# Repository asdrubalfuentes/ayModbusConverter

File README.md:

# ayModbusConverter

**Conversor Modbus TCP ⇄ Modbus RTU (RS-485 y RS-232)** de Aysafi, basado en la placa **WT32-ETH01** (ESP32 + Ethernet LAN8720), con pantalla OLED de 0.96" y configuración web con asistente.

La base es un **servidor Modbus TCP transparente**: cada petición que llega por la LAN se enruta por Unit ID a uno de los dos puertos serie y la respuesta del esclavo vuelve sin tocar. El mapa de memoria es el del equipo RTU conectado. Sobre esa base estándar, Aysafi agrega estados de transmisión visibles, asistente con detección automática, protección del bus (esclavos caídos, caché, solo lectura) e integración con MQTT y API REST.

```
                                                    ┌── P1 RS-485 ──► esclavos (Unit ID 1-100)
 SCADA / HMI / PLC ──LAN (Modbus TCP :502)──► ayModbusConverter
 nube Aysafi ◄── MQTT / API REST ──┘                └── P2 RS-232 ──► equipo (Unit ID 101 → ID 1)
                                        ▲
                teléfono / PC ──WiFi AP (portal cautivo, solo configuración)
```

## Características

### Base estándar

| Área | Detalle |
|---|---|
| LAN (servicio) | Ethernet 10/100. DHCP o IP fija con máscara, puerta de enlace, DNS 1 y 2. Nombre de host, mDNS (`<host>.local`) |
| WiFi | **Solo** punto de acceso con **portal cautivo** para configurar. No transporta tráfico Modbus |
| Modbus TCP | Servidor en :502, hasta 8 clientes, cierre por inactividad, TCP keep-alive, lista blanca de IP/redes. Modbus TCP (MBAP) o RTU sobre TCP |
| Puertos serie | P1 RS-485 (DE/RE por hardware) y P2 RS-232 (o RS-485 autodireccional). 1200 a 230400 bps, 7/8 bits, N/E/O, 1/2 bits de parada |
| Unit ID | Cada puerto atiende un rango de Unit ID con offset. Esclavo fijo opcional. Unit ID 0 = broadcast a todos los puertos |
| Temporización | Timeout, reintentos, fin de trama (t3.5 automático o manual), pausa entre peticiones, pausa tras broadcast, retardo inicial |
| Excepciones | 0x0B (el esclavo no responde), 0x0A (ruta no disponible), 0x01 (solo lectura); desactivables |
| Sistema | Usuario y clave (HTTP Basic), NTP/zona horaria, respaldo y restauración (JSON), valores de fábrica, OTA web y desde GitHub Releases |

### Mejoras Aysafi

| Mejora | Qué hace |
|---|---|
| **Estados de transmisión** | **OK / FALLAS / DESCONECTADO / SIN TRÁFICO** por puerto, por esclavo y global, más **LAN DESCONECTADA**. Se ven en el OLED (página de estado grande que parpadea ante fallas y se enciende sola al cambiar), en el banner del portal y por MQTT |
| **Asistente de puesta en marcha** | Se abre solo en un equipo nuevo: nombre y clave, red LAN, puerto serie con **detección automática**, búsqueda e identificación de equipos, y **ficha de instalación imprimible** |
| **Detección automática del puerto** | Encuentra baudios y paridad. *Activa:* consulta los Unit ID indicados en 24 combinaciones. *Pasiva:* solo escucha el tráfico de otro maestro, sin transmitir |
| **Exploración de equipos** | Lee fabricante, modelo y versión (FC43, si el equipo la soporta) y descubre qué rangos de registros existen, por bloques |
| **Esclavos caídos** | Tras N timeouts seguidos el esclavo queda "caído": se responde 0x0B al instante (sin frenar al resto del bus) y se lo reintenta en segundo plano |
| **Modo caché / agente** | El conversor sondea una tabla de lecturas y responde desde memoria: varios SCADA no saturan un bus lento. Las escrituras invalidan la caché y van directo al esclavo |
| **Aprendizaje del polling** | Anota qué lecturas hace el SCADA y cada cuánto, y las pasa a la tabla de sondeo con un clic |
| **Solo lectura** | Bloquea escrituras a esclavos y rangos de direcciones elegidos (excepción 0x01) |
| **MQTT** | Estado con LWT, valores de la tabla de sondeo y comandos de lectura/escritura (`<base>/cmd`). TLS, por defecto hacia `emqx.aysafi.com` |
| **API REST** | `/api/read`, `/api/write`, `/api/tags` en JSON, con clave de API (`X-API-Key`) o HTTP Basic |
| **Captura para Wireshark** | El monitor de tráfico se descarga como `.pcapng` (RTU y MBAP) |

## Parámetros estándar de la industria

La base sigue los parámetros que tienen en común los conversores comerciales más usados (Moxa MGate MB3180/MB3280, USR-TCP232-410S/USR-M100, Waveshare RS485-to-ETH, Elfin EE11/EW11), con los mismos nombres y comportamiento.

| Parámetro estándar | Moxa | USR | Waveshare/Elfin | ayModbusConverter |
|---|:-:|:-:|:-:|---|
| IP fija / DHCP, máscara, gateway, DNS | ✓ | ✓ | ✓ | Red → LAN |
| Baudios, bits de datos, paridad, bits de parada | ✓ | ✓ | ✓ | Puertos serie |
| Puerto TCP local (502) | ✓ | ✓ | ✓ | Modbus TCP → Puerto |
| Máximo de conexiones | ✓ | ✓ | ✓ | Conexiones simultáneas (1-8) |
| Modbus TCP ⇄ RTU / RTU sobre TCP | ✓ | ✓ | ✓ | Protocolo |
| Timeout de respuesta | ✓ | ✓ | ✓ | Puertos serie → Timeout |
| Timeout entre caracteres / fin de trama | ✓ | ✓ | ✓ | Fin de trama (0 = t3.5) |
| Retardo entre tramas | ✓ | – | ✓ | Pausa entre peticiones |
| Reintentos | ✓ | – | – | Reintentos |
| Retardo inicial | ✓ | – | – | Modbus TCP → Retardo inicial |
| Excepción de pasarela (0x0A/0x0B) | ✓ | ✓ | – | Responder excepciones |
| Mapeo de Unit ID por puerto (rango + offset) | ✓ | – | – | Puertos serie → Enrutamiento |
| TCP alive check | ✓ | ✓ | ✓ | TCP alive check (s) |
| Cierre por inactividad | ✓ | ✓ | ✓ | Cierre por inactividad (s) |
| Lista de IP permitidas | ✓ | – | – | Control de acceso |
| Monitor de tráfico / diagnóstico | ✓ | ✓ | – | Diagnóstico |
| Actualización de firmware web | ✓ | ✓ | ✓ | Sistema → Firmware |
| Respaldo / restauración de la configuración | ✓ | ✓ | – | Sistema → Respaldo |
| Contraseña de administrador | ✓ | ✓ | ✓ | Sistema → Acceso |

## Hardware

### Conexiones (WT32-ETH01 v1.4)

| Función | GPIO | Serigrafía | Conectar a |
|---|---|---|---|
| P1 RS-485 RX | 5 | RXD / IO5 | RO del transceptor RS-485 |
| P1 RS-485 TX | 17 | TXD / IO17 | DI del transceptor RS-485 |
| P1 RS-485 DE//RE | 33 | 485_EN | DE y /RE unidos |
| P2 RS-232 RX | 35 | IO35 | R1OUT del MAX3232 |
| P2 RS-232 TX | 4 | IO4 | T1IN del MAX3232 |
| OLED SDA | 14 | IO14 | SDA del SSD1306 (0x3C) |
| OLED SCL | 15 | IO15 | SCL del SSD1306 |
| Botón | 32 | CFG | pulsador a GND (pull-up interno) |
| LED actividad | 2 | IO2 | LED + 1 kΩ a GND (opcional) |
| Programación | 1 / 3 | TX0 / RX0 | adaptador USB-TTL 3V3 |

- P1: transceptor MAX3485 / SP3485 (3,3 V). Con un MAX485 de 5 V, pon un divisor en RO.
- P2: MAX3232 a 3,3 V. T1OUT → RX del equipo, R1IN ← TX del equipo, GND común (en un DB9 estándar: pin 2 RX, 3 TX, 5 GND; si no hay comunicación, cruza 2 y 3). También acepta un módulo RS-485 **autodireccional**: no queda ningún GPIO de salida libre para un DE.
- Termina el bus RS-485 con 120 Ω en ambos extremos. Usa par trenzado con malla y referencia GND común.
- No uses los GPIO 0, 16, 18, 19, 21, 22, 23, 25, 26 ni 27: los usa la PHY Ethernet. El GPIO 12 debe estar en bajo al arrancar.

Detalle pin a pin, variantes de módulos y banco de pruebas: [test/README.md](test/README.md).

### Botón

| Pulsación | Acción |
|---|---|
| Corta | Siguiente página del OLED / despierta la pantalla |
| 3 s | Activa el punto de acceso de configuración |
| 10 s | Restaura los valores de fábrica y reinicia |

### Páginas del OLED

| # | Página | Contenido |
|---|---|---|
| 0 | Estado | OK / FALLAS / DESCONECTADO / SIN LAN en grande (parpadea ante fallas) y estado de cada puerto |
| 1 | Red | IP de la LAN, velocidad, AP y portal |
| 2 | Puertos | formato serie, rango de Unit ID y caché de cada puerto; clientes TCP |
| 3 | Esclavos | estado de cada esclavo visto |
| 4 | Tráfico | peticiones, OK, timeouts, CRC, excepciones, caché, latencia |
| 5 | Sistema | versión, tiempo encendido, memoria, MAC |

Un cambio de estado (cable de red, puerto que empieza a fallar o se recupera) enciende la pantalla y salta a la página de estado.

## Primer arranque

1. Conecta la LAN (DHCP por defecto) o el WiFi **`ayModbus-XXXXXX`** (clave `aysafi1234`; el portal se abre solo).
2. Entra a la IP que muestra el OLED o a `http://aymc-xxxxxx.local`. Usuario **admin**, clave **admin**.
3. El **asistente** se abre solo: nombre y clave, red, puerto serie (con *Detectar automáticamente*), búsqueda de equipos y resumen para imprimir. Al finalizar, el equipo se reinicia.

Desde el portal WiFi (red WPA2) no se pide usuario ni clave, porque los navegadores de portal cautivo de los teléfonos no manejan bien HTTP Basic. Si la clave del AP está vacía, se pide igual.

## Valores de fábrica

| Parámetro | Valor |
|---|---|
| LAN | DHCP, host `aymc-<id>` |
| AP | siempre activo, `ayModbus-<ID>` / `aysafi1234`, canal 6 |
| P1 RS-485 | habilitado, 9600 8N1, timeout 1000 ms, Unit ID 1-247, caído tras 3 timeouts (reintento 10 s) |
| P2 RS-232 | deshabilitado, 9600 8N1, Unit ID 101-147 con offset -100. Al habilitarlo, la web ajusta P1 a 1-100 |
| Modbus TCP | :502, MBAP, 4 clientes, inactividad 300 s, keep-alive 60 s, excepciones sí |
| Caché, MQTT, API key | desactivados |
| Acceso web | admin / admin |

## Compilar y programar

```bash
pio run
```

La WT32-ETH01 no tiene USB. Para la primera carga, conecta un adaptador USB-TTL de 3,3 V a TX0/RX0/GND, pon **IO0 a GND**, reinicia (EN) y ejecuta:

```bash
pio run -t upload
```

Las cargas siguientes se hacen por OTA desde **Sistema → Firmware** (`.pio/build/wt32-eth01/firmware.bin`).

Para probar la interfaz web sin la placa (usa la UI embebida y simula la API, herramientas incluidas):

```bash
python test/webmock/mock.py --wizard
```

## Publicar una versión (OTA GitHub)

1. Anota el cambio en `CHANGELOG.md` y sube `FW_SEMVER` en `src/fw_version.h`.
2. Etiqueta sobre `main`: `git tag v1.1.0 && git push origin v1.1.0`.
3. El workflow `.github/workflows/release.yml` compila y publica `firmware.bin`, `version.txt` y `firmware.sha256` como Release *latest*.
4. Los equipos con salida a internet lo instalan con **Sistema → Instalar desde GitHub**, o solos al arrancar si está activado.

El repositorio debe ser **público** para que los equipos descarguen los Releases sin token.

## MQTT

Raíz de tópicos por defecto: `aysafi/<host>`.

| Tópico | Dirección | Contenido |
|---|---|---|
| `<base>/status` | publica (retenido) | `{online, name, fw, ip, lan, state, ports[], slaves[], stats}`; cada N s y al cambiar un estado. LWT `{"online":false}` |
| `<base>/data/<nombre>` | publica | valores de cada lectura de la tabla de sondeo marcada *MQTT*: `{v:[...], q, age, uid, fc, addr, ts}` |
| `<base>/cmd` | suscribe (opcional) | `{"id":7,"uid":1,"fc":3,"addr":0,"qty":10}` o escritura `{"uid":1,"fc":6,"addr":10,"value":123}` (`port` opcional) |
| `<base>/cmd/resp` | publica | `{id, ok, result, values / exception, lat}` |

## API REST

Todas las rutas usan HTTP Basic, salvo que la petición llegue desde el AP. Las marcadas con * aceptan también la cabecera `X-API-Key` (o `?key=`).

| Método | Ruta | Uso |
|---|---|---|
| GET | `/api/status` | Estado global y por puerto/esclavo, red, contadores, clientes, MQTT |
| GET | `/api/read`* | `?uid=1&fc=3&addr=0&qty=10[&port=1][&cache=0]` lectura (enruta por Unit ID si no hay `port`) |
| POST | `/api/write`* | `{uid, fc(5/6/15/16), addr, value / values[, port]}` |
| GET | `/api/tags`* | Tabla de sondeo con sus últimos valores |
| GET / POST | `/api/config` | Leer / guardar la configuración (JSON parcial; reinicia) |
| POST | `/api/port/apply` | `{port, cfg:{...}}` aplica un puerto sin reiniciar |
| GET / POST | `/api/tool` | Herramientas: `{kind:"scan"|"detect"|"discover"|"apply"|"stop", port, ...}` y su progreso |
| GET / POST | `/api/learn` | Aprendizaje del polling: resultados / `{en, clear}` |
| GET / POST | `/api/monitor` | Tramas desde `?since=N` / `{en, clear}` |
| GET | `/api/pcap` | Monitor como captura `.pcapng` |
| POST | `/api/test` | `{port, uid, fc, addr, qty, value, values}` lectura/escritura directa |
| GET | `/api/backup` · POST `/api/restore` | Respaldo / restauración (reinicia) |
| POST | `/api/stats/reset`, `/api/reboot`, `/api/factory`, `/api/wizard/done` | Mantenimiento |
| POST | `/api/fw` · `/api/ota` | Firmware por archivo / desde GitHub |

## Estructura

```
src/
  main.cpp          arranque, botón, OTA GitHub
  config.*          configuración en NVS como JSON (sobrevive a cambios de versión)
  net.*             LAN (LAN8720) + AP con portal cautivo, mDNS, NTP
  modbus_rtu.*      puerto RTU (clase por puerto): CRC, fin de trama, reintentos, escucha pasiva
  gateway.*         tareas TCP y por puerto, colas, enrutamiento, salud/estados, caché,
                    aprendizaje, solo lectura, escaneo/autodetección/exploración, monitor y pcap
  mb_util.*         armado de peticiones y respuestas JSON (web, REST, MQTT)
  mqtt_bridge.*     puente MQTT
  web.*, web_ui.h   API REST + interfaz web embebida (con asistente)
  display.*         OLED SSD1306 (páginas de estado)
  ota_update.*      OTA desde GitHub Releases
test/webmock/       servidor para probar la UI sin la placa
test/tools/         simulador de esclavos RTU + batería de pruebas automática
```

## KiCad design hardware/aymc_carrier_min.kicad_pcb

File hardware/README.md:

# PCB base — ayModbusConverter MINI

Rev E · KiCad 8 · **70 × 58 mm**, dos capas

Placa reducida al mínimo práctico, atornillada al chasis, que a su vez va al riel DIN por los anclajes. La
WT32-ETH01 se enchufa en dos zócalos de 13 pines con el **eje largo vertical**: el RJ45
sale por la pared superior del chasis y la bornera por la inferior. La tapa solo lleva el
agujero del LED de enlace.

---

## 1. Qué lleva

| Ref | Valor | Función |
|---|---|---|
| J1 | Bornera 4 vías, paso 5,08 | A, B, +V (9–24 VDC), GND |
| J2, J3 | Zócalo hembra 1×13, paso 2,54 | WT32-ETH01, filas a **22,86 mm** |
| U1 | 7805 TO-220 | +V → 5 V |
| U2 | MAX485 DIP-8 | Transceptor RS-485 half duplex |
| C1 | 100 µF / 25 V | Salida del regulador |
| C2 | 0,33 µF | Entrada del regulador |
| C3 | 100 nF | Desacoplo del MAX485 |
| R1 | 120 Ω | Terminación entre A y B |
| R2, R3 | 1 k / 2 k | Divisor de RO, 5 V → 3,3 V |
| R4 | 1 k | Limitador del LED |
| D1 | LED 3 mm | Enlace Modbus |

La bornera admite AWG18 sin problema: taladro de 1,3 mm y pad de 2,8 mm.

---

## 2. Tres cosas que cambié respecto a lo pedido

### 2.1 Separación de los zócalos: 22,86 mm, no 24

La cota real del módulo son **22,86 mm** (0,9 pulgadas), verificada contra la huella del
datasheet V1.4. Con 24 mm el módulo sencillamente no entra: son 1,14 mm de desalineación
repartidos en 13 pines. Además 24 / 2,54 = 9,45, o sea que 24 mm ni siquiera cae en la
rejilla de 2,54 en la que están los pines.

Es el único punto donde no seguí la indicación al pie de la letra, y lo hice porque la
alternativa era una placa inservible.

### 2.2 Divisor R2 / R3 en RO

No estaba en tu lista, pero es obligatorio. El MAX485 alimentado a 5 V saca **RO a 5 V**,
y esa señal entra en IO5 del ESP32, que es de 3,3 V. Sin divisor se destruye la entrada.
R2 de 1 k y R3 de 2 k la dejan en 3,33 V.

Si prefieres quitar los dos resistores, cambia el MAX485 por un **MAX3485 o SP3485**
(mismo pinout DIP-8) alimentado a 3,3 V desde el propio módulo. Son dos componentes menos
y una fuente de error menos.

### 2.3 Condensador de salida: 25 V, no 6 V

Pediste 100 µF / 6 V sobre un bus de 5 V. Eso es 1,2× de margen, cuando lo habitual es
1,5× a 2×. Los electrolíticos pierden capacidad con la temperatura y la edad, y dentro de
un tablero cerrado envejecen rápido. Puse 25 V, que no cuesta más ni ocupa mucho más.

---

## 3. El 7805 es el punto débil de esta placa

Lo monté como pediste, pero conviene saber lo que implica:

| Entrada | 150 mA | 250 mA | 350 mA |
|---|---|---|---|
| 9 V | 0,60 W | 1,00 W | 1,40 W |
| 12 V | 1,05 W | 1,75 W | 2,45 W |
| 24 V | 2,85 W | **4,75 W** | **6,65 W** |

El consumo del WT32-ETH01 con Ethernet activo y picos de WiFi está entre 150 y 350 mA.

A 24 V de entrada el regulador tiene que disipar entre 3 y 7 W. Un TO-220 sin disipador
aguanta algo más de 1 W antes de superar los 100 °C de encapsulado. Con 7 W dentro de una
caja de inoxidable cerrada, el 7805 entra en protección térmica y el equipo se reinicia en
bucle.

Tres salidas, de menos a más trabajo:

1. **Alimentar a 9 V.** Dentro del rango que pediste y la disipación baja a 1 W. Con un
   disipador pequeño funciona.
2. **Sustituir por un K7805-2000R3.** Es un convertidor conmutado con el **mismo pinout
   SIP-3** que el 7805, así que entra en la misma huella sin tocar la placa. Rendimiento
   del 90 %, disipa menos de 0,2 W a 24 V. Cuesta unas pocas veces más que un 7805 y
   resuelve el problema entero.
3. **Dejar el 7805 con disipador** y limitar la entrada a 12 V.

La huella que puse admite las tres: los tres pines son IN, GND, OUT a paso 2,54.

---

## 4. El LED de enlace

D1 está en la posición (66, 52) de la placa, que en la caja queda a **Y = −17,3 mm,
Z = +18,5 mm** respecto al centro de la tapa.

Lo mueve IO2, que en el firmware es `PIN_LED_ACT`: parpadea con cada trama Modbus válida.
Entre paquetes queda apagado, así que un parpadeo continuo significa que hay polling en
ambos extremos, que es justo lo que querías ver.

**Necesita guía de luz.** Desde la cara superior del PCB hasta la cara interior de la tapa
hay 32,4 mm. Un LED de 3 mm soldado a ras no llega ni de lejos. Dos opciones: una guía de
luz de 3 mm de ese largo, o montar el LED sobre patillas largas de modo que la cápsula
quede a ras de la tapa. La segunda es más frágil pero no cuesta nada.

---

## 5. Ruteado

Dos capas, con plano de masa en ambas. No hay vías de señal: todos los componentes son de
agujero pasante, así que cada pad une las dos capas por sí mismo.

| Capa | Nets |
|---|---|
| F.Cu | +5V, RS485_B, P1_RO, P1_DI, RO_RAW, LED_D, LED_A |
| B.Cu | +VIN, RS485_A, P1_DE |

Tres nets van por la cara inferior porque sus cruces son topológicamente inevitables: A y B
se cruzan entre el MAX485 y la bornera, y DE cruza a RO y DI porque el orden de los pines
del MAX485 es el inverso del orden de los pines del módulo.

Anchos: 1,0 mm en alimentación, 0,5 mm en señal.

### Verificación automática

El generador comprueba, antes de escribir el archivo:

- pads que se solapan
- pistas que pasan sobre pads de otra red
- cruces entre pistas de distinta red en la misma capa
- pads con red pero sin pista que los toque
- componentes fuera del contorno

Las cinco pasan. Cuatro de ellas fallaron en la primera pasada y señalaron errores reales:
la pista de +5 V pasaba por encima del pad de masa del propio C1, y la del LED bajaba justo
por la columna de pads de la fila B y pisaba el pin 14.

---

## 6. Conexiones al módulo

| Pin del módulo | Señal | Va a |
|---|---|---|
| 7 (IO5) | RO | Divisor R2/R3 |
| 8 (IO17) | DI | U2 pin 4 |
| 6 (IO33) | DE + RE̅ | U2 pines 2 y 3 |
| 12 | 5 V | Salida del 7805 |
| 15 (IO2) | LED | R4 → D1 |
| 2, 9, 11, 14, 23 | GND | Plano |

Coinciden con `src/board.h` del firmware. Los demás pines quedan sin conectar.

---

## 7. Lo que esta placa no lleva

Por simplificar quedaron fuera tres cosas que conviene tener presentes:

- **Sin cabecera de programación.** La primera grabación hay que hacerla con el módulo
  fuera de la placa, con un adaptador USB-TTL. Después todo va por OTA.
- **Sin botón CFG.** El firmware usa IO32 para levantar el AP de WiFi y para los valores de
  fábrica. Sin botón, la configuración es solo por Ethernet o por la consola serie del
  módulo desenchufado.
- **Sin protección de entrada.** No hay fusible, ni diodo antiinversión, ni TVS en el bus.
  Si el equipo va a un tablero industrial con maniobra inductiva cerca, merece la pena
  añadir al menos una SM712 entre A, B y GND.

Ninguna impide que funcione; las tres son decisiones conscientes.

---

## 8. Archivos

| Archivo | Contenido |
|---|---|
| `aymc_carrier_min.kicad_pcb` | Placa ruteada |
| `aymc_carrier_min.kicad_sch` | Esquema |
| `aymc.kicad_sym` | Símbolos |
| `pcb_preview.png` | Vista del trazado |
| `netlist.csv` | 11 redes |
| `bom.csv` | Lista de materiales |
| `tools/gen_pcb.py` | Genera placa, netlist y BOM, y verifica el ruteado |
| `tools/gen_sch.py` | Genera el esquema desde la misma tabla |

Esquema y placa salen de **una sola tabla de componentes y redes**, así que no pueden
desincronizarse. Si cambias algo, cámbialo en `gen_pcb.py` y vuelve a ejecutar los dos.

---

## 9. Reducción respecto a la Rev D

| Concepto | Rev D | Rev E | Reducción |
|---|---|---|---|
| Placa | 95 × 72 mm | **70 × 58 mm** | 41 % de área |
| Interior de la caja | 104 × 82 × 40 | **78 × 68 × 36** | 44 % de volumen |
| Chapa bruta | 366 cm² | **249 cm²** | 32 % |
| Masa de inoxidable | 289 g | **197 g** | 32 % |

Qué permitió apretarla:

- El MAX485, el divisor y la terminación se agruparon en la columna derecha junto a la
  bornera, en vez de repartirse por la placa.
- Los taladros de fijación pasaron a 5 mm del borde y la alimentación cruza por el borde
  superior, a 2,5 mm, que es donde no estorba a nada.
- El ancho de pista en señal bajó a 0,25 mm, lo justo para pasar entre pads a paso 2,54
  con 0,2 mm de holgura. La alimentación se mantiene en 0,8 mm.

El límite ahora lo pone el propio módulo: 60 mm de largo con el RJ45 asomando, más la
bornera debajo sin solaparse con él. Para bajar de 58 mm de alto habría que mover la
bornera a un costado, y entonces saldría por la tapa en vez de por el chasis.

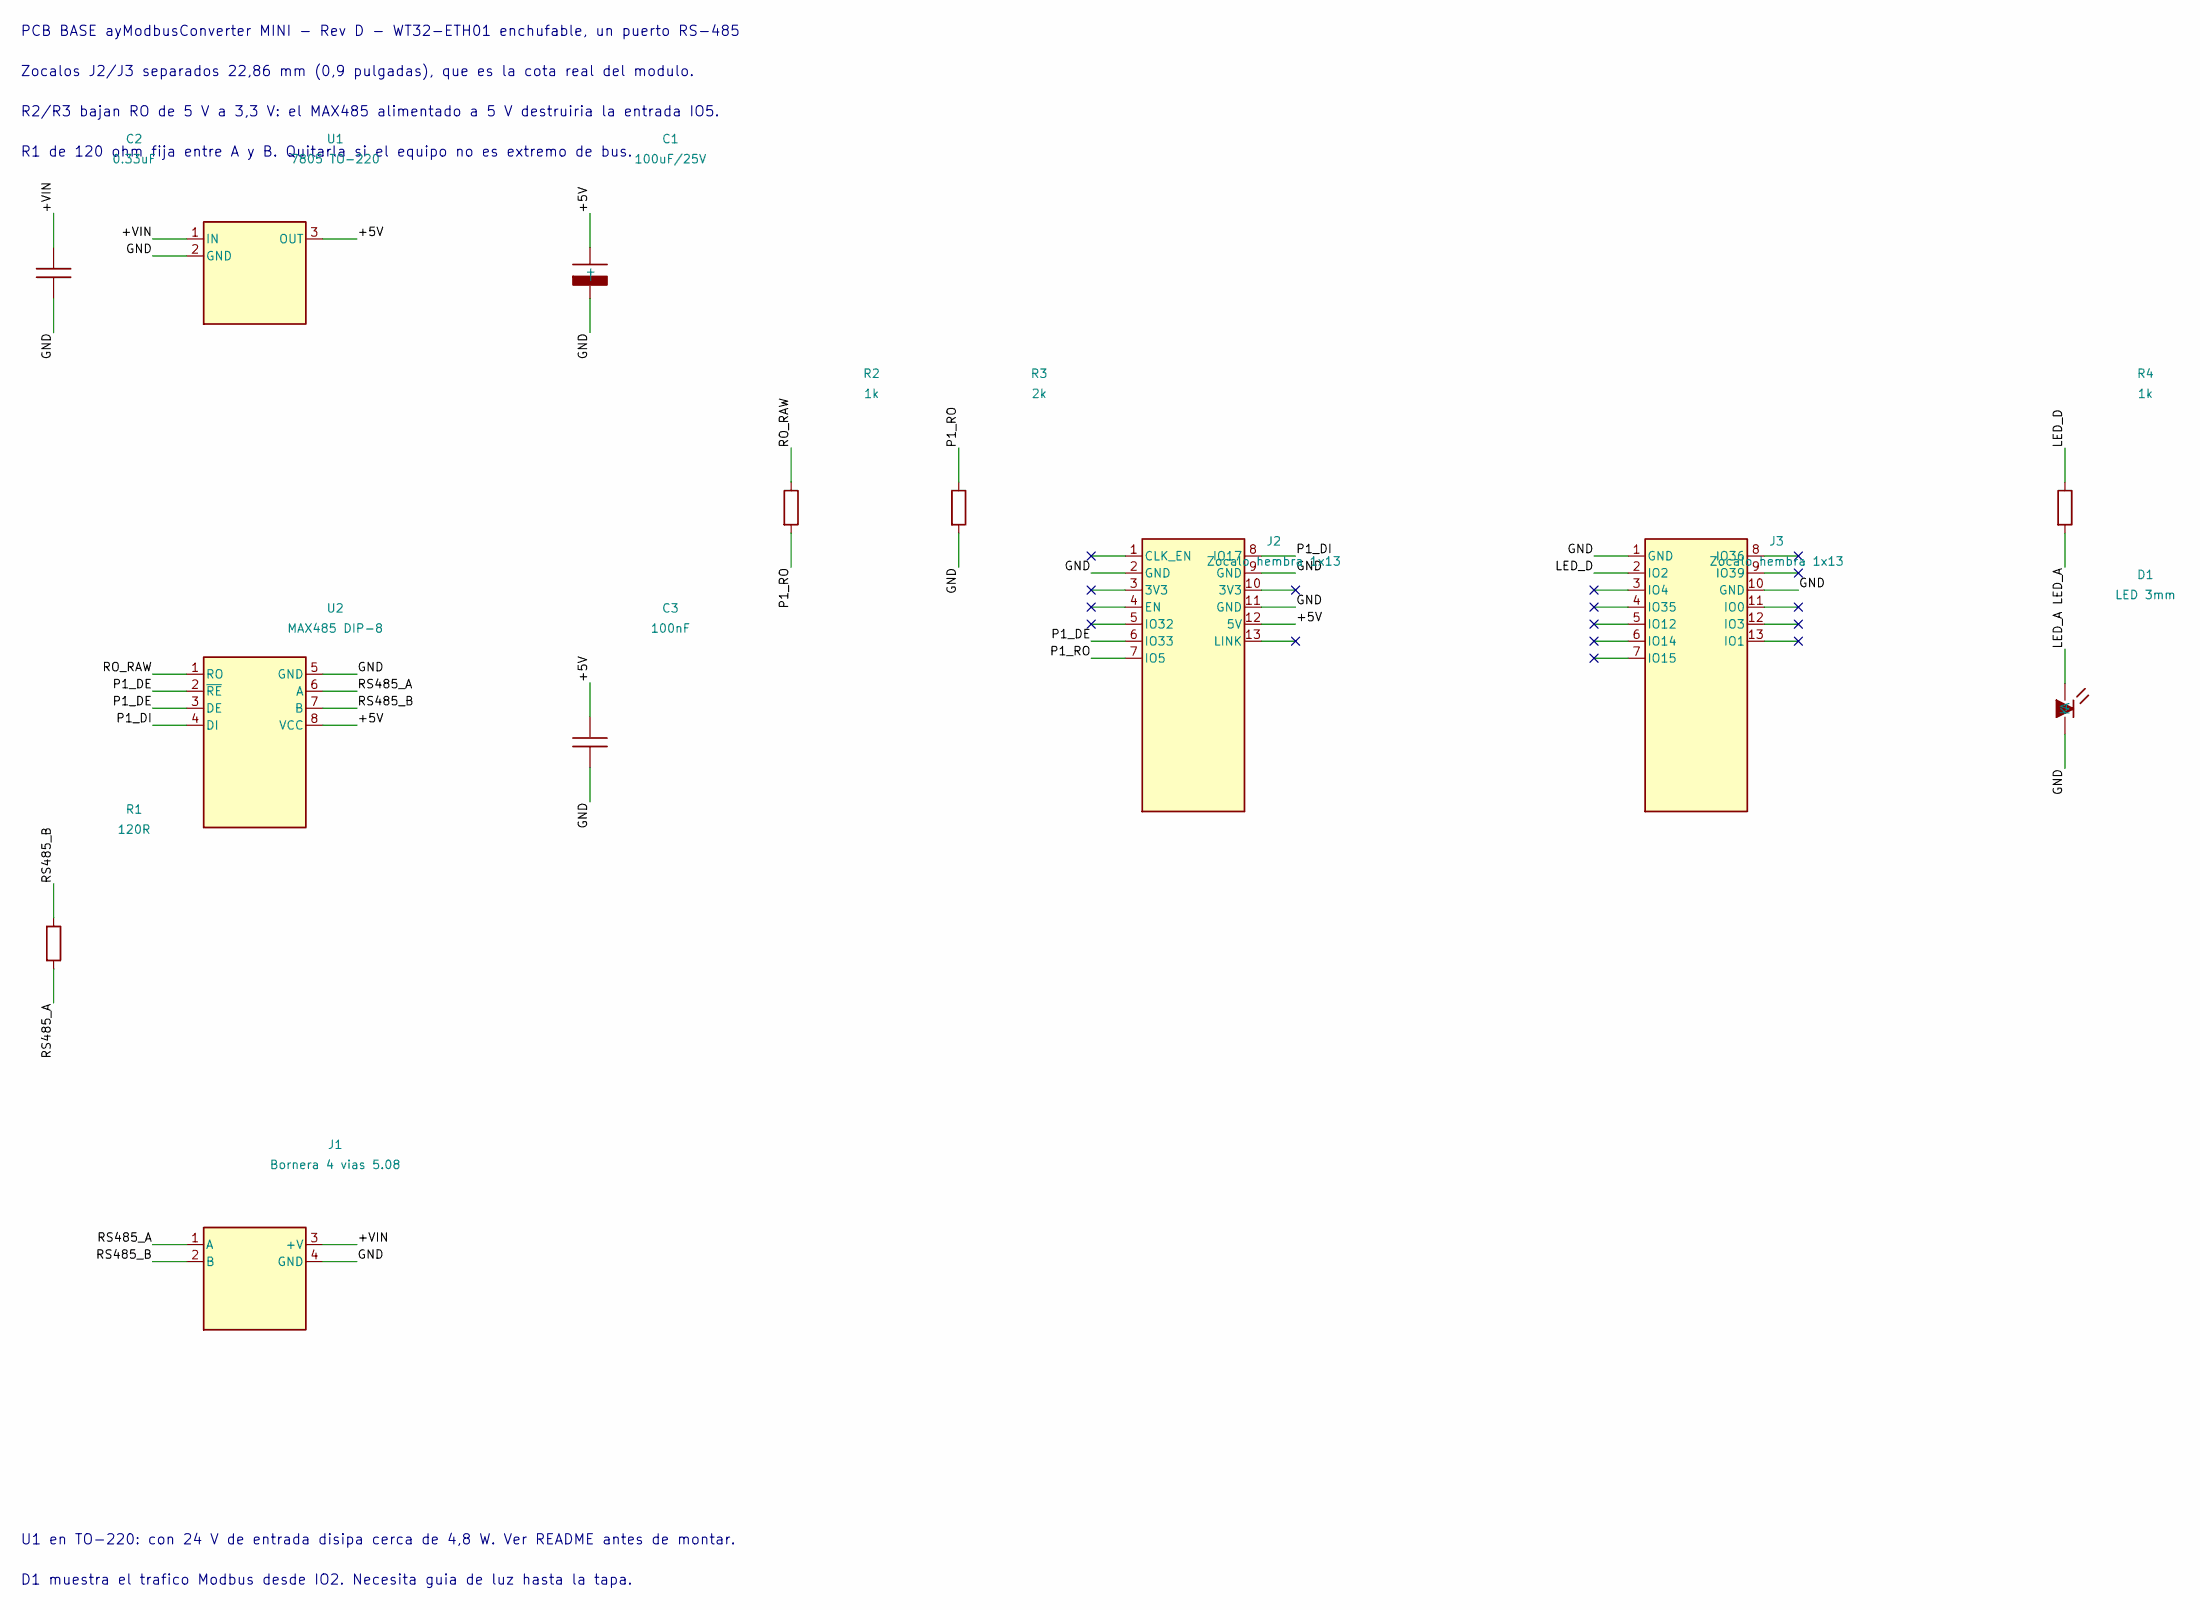
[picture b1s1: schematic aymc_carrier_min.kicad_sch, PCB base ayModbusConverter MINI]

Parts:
C1: 100uF/25V
C2: 0.33uF
C3: 100nF
D1: LED 3mm
J1: Bornera 4 vias 5.08
J2, J3: Zocalo hembra 1x13
R1: 120R
R2, R4: 1k
R3: 2k
U1: 7805 TO-220
U2: MAX485 DIP-8

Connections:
+5V: C1.1 (+), C3.1, J2.12 (5V), U1.3 (OUT), U2.8 (VCC)
+VIN: C2.1, J1.3 (+V), U1.1 (IN)
GND: C1.2 (-), C2.2, C3.2, D1.2 (K), J1.4 (GND), J2.2 (GND), J2.9 (GND), J2.11 (GND), J3.1 (GND), J3.10 (GND), R3.2, U1.2 (GND), U2.5 (GND)
LED_A: D1.1 (A), R4.2
LED_D: J3.2 (IO2), R4.1
P1_DE: J2.6 (IO33), U2.2 (~RE), U2.3 (DE)
P1_DI: J2.8 (IO17), U2.4 (DI)
P1_RO: J2.7 (IO5), R2.2, R3.1
RO_RAW: R2.1, U2.1 (RO)
RS485_A: J1.1 (A), R1.2, U2.6 (A)
RS485_B: J1.2 (B), R1.1, U2.7 (B)

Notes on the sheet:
PCB BASE ayModbusConverter MINI - Rev D - WT32-ETH01 enchufable, un puerto RS-485
Zocalos J2/J3 separados 22,86 mm (0,9 pulgadas), que es la cota real del modulo.
R2/R3 bajan RO de 5 V a 3,3 V: el MAX485 alimentado a 5 V destruiria la entrada IO5.
R1 de 120 ohm fija entre A y B. Quitarla si el equipo no es extremo de bus.
U1 en TO-220: con 24 V de entrada disipa cerca de 4,8 W. Ver README antes de montar.
D1 muestra el trafico Modbus desde IO2. Necesita guia de luz hasta la tapa.

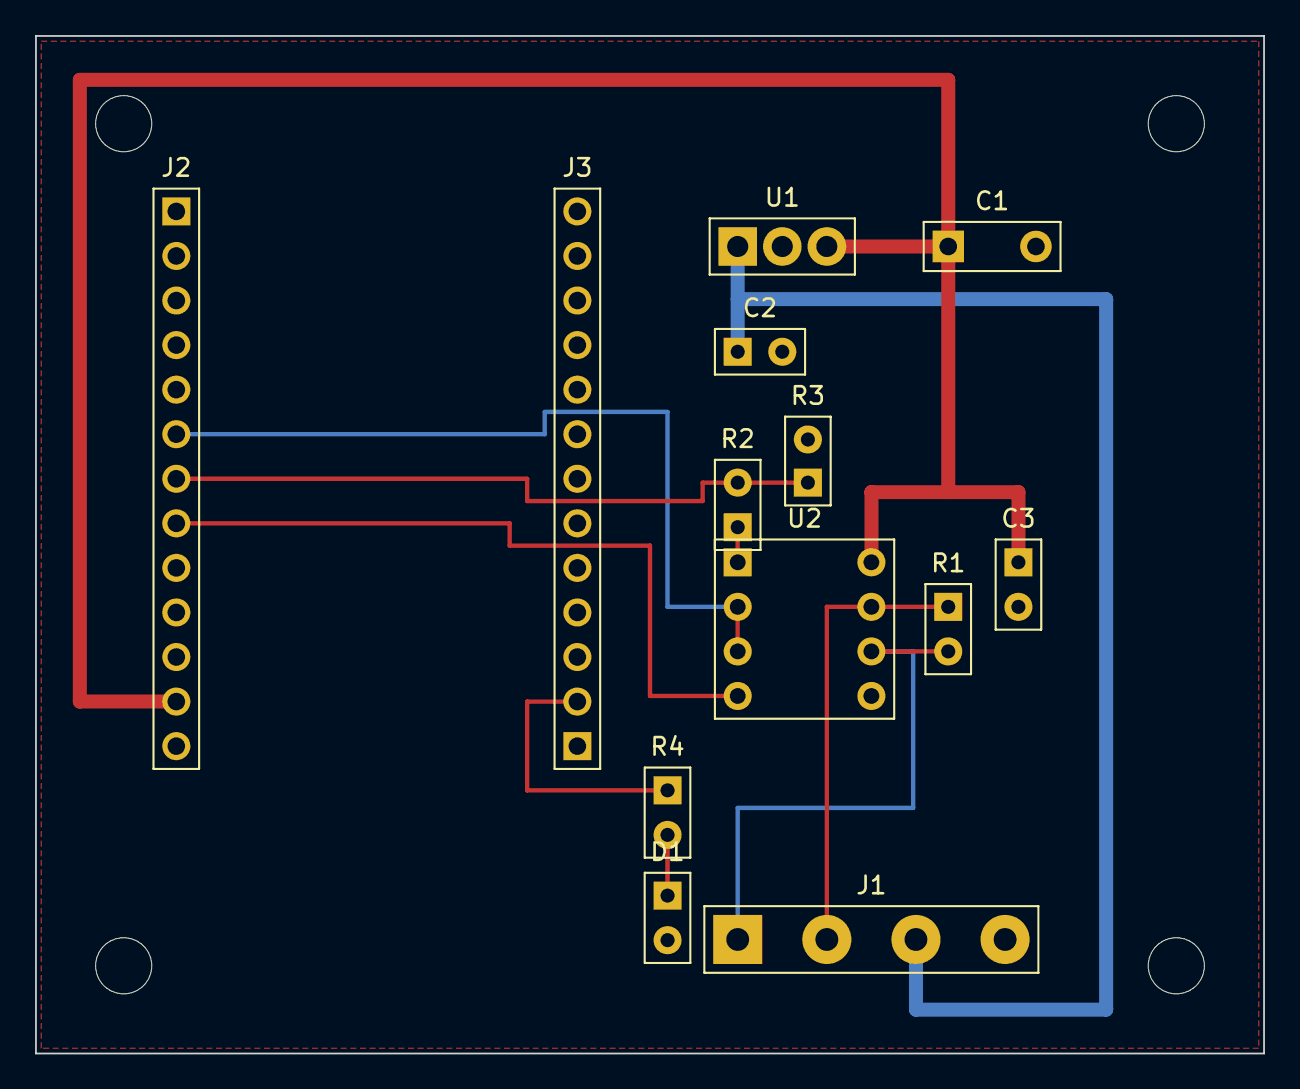
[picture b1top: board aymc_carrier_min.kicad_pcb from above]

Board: 2 copper layers, 70.0 x 58.0 mm, 13 parts (0 on the bottom side), 11 nets.

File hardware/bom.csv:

Ref,Valor,Huella,Descripcion
J1,Bornera 4 vias 5.08,TERM4,A / B / +V(9-24Vdc) / GND
J2,Zocalo hembra 1x13,HDR13,"Fila A del WT32-ETH01, pines 1-13"
J3,Zocalo hembra 1x13,HDR13,"Fila B del WT32-ETH01, pines 14-26"
U1,7805 TO-220,TO220,Regulador +V -> 5V (admite K7805-2000R3)
C2,0.33uF,CER254,Entrada
C1,100uF/25V,ELEC5,Salida
C3,100nF,CER254,Desacoplo MAX485
U2,MAX485 DIP-8,DIP8,Transceptor RS-485 half duplex
R2,1k,AXIAL254,Divisor RO sup.
R3,2k,AXIAL254,Divisor RO inf.
R1,120R,AXIAL254,Terminacion de linea
R4,1k,AXIAL254,Limitador LED
D1,LED 3mm,LED254,Enlace Modbus
